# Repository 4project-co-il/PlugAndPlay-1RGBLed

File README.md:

# PlugAndPlay: Module with 1 RGB LED
This is the repository with the files for PlugAndPlay module with 1 RGB LED.

The LED is controlled via TI's LP5815 driver, with shutdown control via INT1 line.

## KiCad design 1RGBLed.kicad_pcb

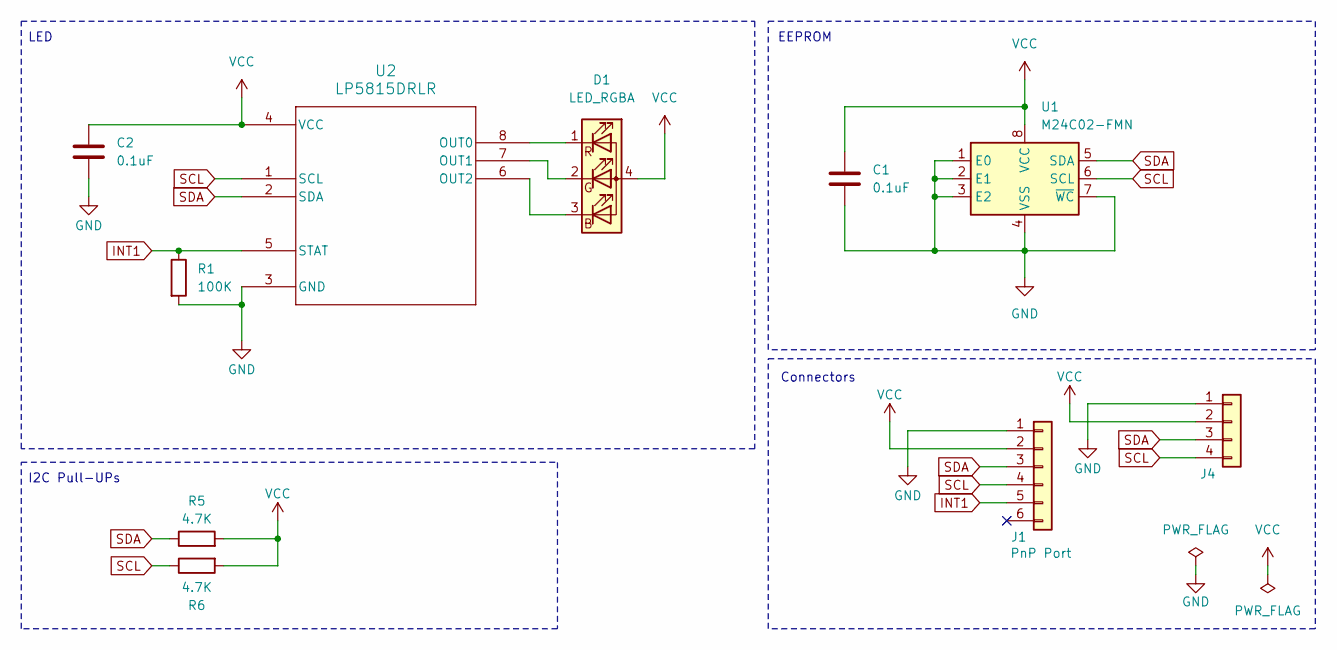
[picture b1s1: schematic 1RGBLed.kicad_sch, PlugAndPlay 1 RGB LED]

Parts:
C1, C2: 0.1uF; C_0603_1608Metric; MPN C14663
D1: LED_RGBA; LED_LiteOn_LTST-C19HE1WT; MPN C458749
J1: JST_SH_SM06B-SRSS-TB_1x06-1MP_P1.00mm_Horizontal; MPN C7430448
J4: Conn_01x04; PogoPinsPads_1x04_P2.5mm
R1: 100K; R_0603_1608Metric_Pad0.98x0.95mm_HandSolder
R5, R6: 4.7K; R_0603_1608Metric; MPN C4190
U1: M24C02-FMN; SOIC-8_3.9x4.9mm_P1.27mm; MPN C114502
U2: LP5815DRLR; SOT23-8_5X3_TEX; MPN C47262831

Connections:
GND: C1.2, C2.2, J1.1, J4.1, R1.2, U1.1 (E0), U1.2 (E1), U1.3 (E2), U1.4 (VSS), U1.7 (~WC), U2.3 (GND)
INT1: J1.5, R1.1, U2.5 (STAT)
unnamed: D1.3 (BK), U2.6 (OUT2)
unnamed: D1.2 (GK), U2.7 (OUT1)
unnamed: D1.1 (RK), U2.8 (OUT0)
SCL: J1.4, J4.4, R6.1, U1.6 (SCL), U2.1 (SCL)
SDA: J1.3, J4.3, R5.1, U1.5 (SDA), U2.2 (SDA)
VCC: C1.1, C2.1, D1.4 (A), J1.2, J4.2, R5.2, R6.2, U1.8 (VCC), U2.4 (VCC)

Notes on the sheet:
EEPROM
LED
Connectors
I2C Pull-UPs

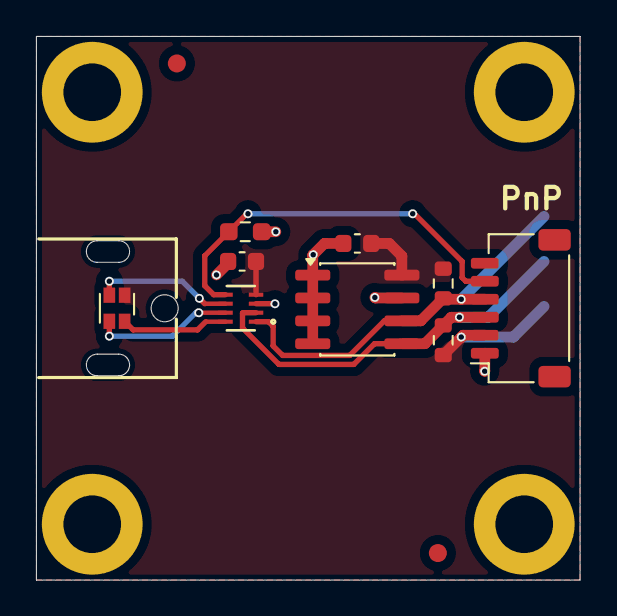
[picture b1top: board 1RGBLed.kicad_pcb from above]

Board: 2 copper layers, 30.2 x 30.2 mm, 10 parts (1 on the bottom side), 8 nets.
